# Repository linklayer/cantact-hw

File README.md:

# CANtact Hardware

This repository contains the hardware design files for the CANtact tool. They 
can be opened and edited with [KiCad](http://www.kicad.org/).

Documentation can be found on the [Linklayer Wiki](https://wiki.linklayer.com/index.php/CANtact).

A PDF of the schematic is available
[here](https://github.com/CANtact/cantact-hw/blob/master/cantact.pdf?raw=true).

## Official Retailers

- [Linklayer Store](https://store.linklayer.com) (USA)
- [Hacker Warehouse](https://hackerwarehouse.com) (USA)
- [VETEC](http://vctec.co.kr) (South Korea)

## License

Hardware files released under the [Creative Commons Attribution-ShareAlike 4.0
International License](http://creativecommons.org/licenses/by-sa/4.0/) (CC BY-SA
4.0)

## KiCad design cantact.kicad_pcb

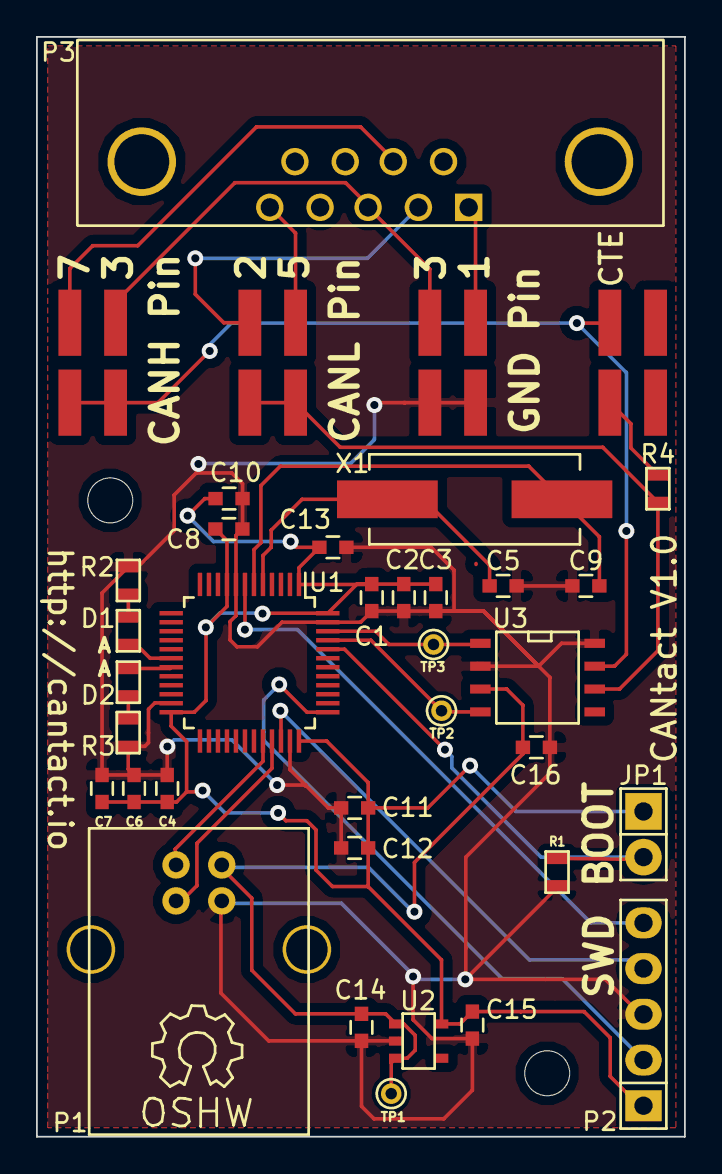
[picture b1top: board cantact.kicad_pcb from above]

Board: 2 copper layers, 36.0 x 61.1 mm, 38 parts (0 on the bottom side), 25 nets.

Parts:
C1, C2, C4, C6, C11, C13, C16: 0.1uF; C_0603
C3, C7, C12: 4.7uF; C_0603
C5, C9: 18pF; C_0603
C8: 10nF; C_0603
C10, C14, C15: 1uF; C_0603
D1, D2: LED; SMD-0603
JP1: Boot Mode; Pin_Header_Straight_1x02
JP2: Term Enable; 0015912040
JP3: CANH Select; 0015912040
JP4: CANL Select; 0015912040
JP5: GND Select; 0015912040
P1: USB; USB_B
P2: SWD; Pin_Header_Straight_1x05
P3: DB9; DB9MC
R1: 510; SMD-0603
R2, R3: R; SMD-0603
R4: 120; SMD-0603
SYM: Symbol_OSHW-Logo_SilkScreen_07Jul2012; Symbol_OSHW-Logo_SilkScreen
TP1, TP2, TP3: TST; PINTST
U1: STM32F042C6T6; LQFP-48_7x7mm_Pitch0.5mm
U2: AAT3221; SOT-23-5
U3: MCP2551-I/SN; SOIC-8-N
X1: 16 MHz; Crystal_HC49-SD_SMD

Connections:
+3.3V: C1.1, C2.1, C3.1, C4.1, C6.1, C7.1, C8.1, C10.1, C11.1, C12.1, C13.1, C15.1, JP1.1, P2.1, U1.1, U1.9, U1.24, U1.36, U1.48, U2.5
+5V: C14.1, C16.2, P1.1, TP1.1, U2.1, U2.3, U3.3
/CAN_RX: TP2.1, U1.45, U3.4
/CAN_TX: TP3.1, U1.46, U3.1
/DB9_1: JP5.4, P3.1
/DB9_2: JP4.2, P3.2
/DB9_3: JP3.4, JP5.2, P3.3
/DB9_5: JP4.4, P3.5
/DB9_7: JP3.2, P3.7
/NRST: P2.5, U1.7
/SWCLK: P2.2, U1.37
/SWDIO: P2.4, U1.34
/USB_DM: P1.2, U1.32
/USB_DP: P1.3, U1.33
GND: C1.2, C2.2, C3.2, C4.2, C5.2, C6.2, C7.2, C8.2, C9.2, C10.2, C11.2, C12.2, C13.2, C14.2, C15.2, C16.1, JP5.1, JP5.3, P1.4, P2.3, R1.2, R2.1, R3.1, U1.8, U1.23, U1.35, U1.47, U2.2, U3.2, U3.8
unnamed: C5.1, U1.5, X1.1
unnamed: C9.1, U1.6, X1.2
unnamed: D1.1, U1.18
unnamed: D1.2, R2.2
unnamed: D2.1, U1.19
unnamed: D2.2, R3.2
unnamed: JP1.2, R1.1, U1.44
unnamed: JP2.1, R4.2
unnamed: JP2.2, JP3.1, JP3.3, U3.7
unnamed: JP4.1, JP4.3, R4.1, U3.6

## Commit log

2015-01-14 initial commit, hardware v0.2
2015-01-14 hardware v0.3, added mounting holes and text
2015-01-14 added readme
2015-02-07 added v1.0 draft BOM
2015-02-09 updated BOM and added PDF version
2015-02-09 changed BOM to landscape
2015-05-26 final v1.0 fixes, added assembly files
2015-05-26 removed pdf bom
2017-06-09 added doc link and retailers
2021-11-08 Update README.md
    https://forum.kicad.info/t/warning-avoid-all-links-to-kicad-pcb-org-use-kicad-org/31521
